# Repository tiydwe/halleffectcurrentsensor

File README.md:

# Handheld Hall Effect Current Sensor

This is a handheld hall effect current sensor, a device used to measure current without needing to directly touch the circuit being measured.

# Features
* Completely contained on one handheld case, including battery
* Self powered!
* OLED screen for easy measurement
* Two adjustable calibration resistors for easy calibration

# Assembly
The handheld hall effect current sensor is easily assembled with just 4 parts:
* The bottom part of case
* The battery, which sits in the bottom part of case
* The PCB, which goes between the top and bottom part of the case
* The top part of the case

It is held together with 4 M2 screws and 4 M2 nuts.

# Technical stuff

The hall effect voltage output is fed into an insturmentation amplifier to subtract it from the known zero current voltage and amplify the result. Both the gain and the reference voltage can be easily adjusted with two variable resistors on the PCB. The output of the insturmentation amplifier goes into a Seeed Studio nrf52840 microcontroller's ADC where it is processed. The current reading is then written onto the OLED.

The whole system is powered from a lipo battery, which is regulated to 3.3v by the Seeed Studio microcontroller. An additional [3.3v to 5v off-board converter](https://www.amazon.com/Comidox-Module-Voltage-Converter-0-9-5V/dp/B07L76KLRY/) is used to power the op amp and hall effect sensor.

# IMAGES
Full schematic:

PCB layout:

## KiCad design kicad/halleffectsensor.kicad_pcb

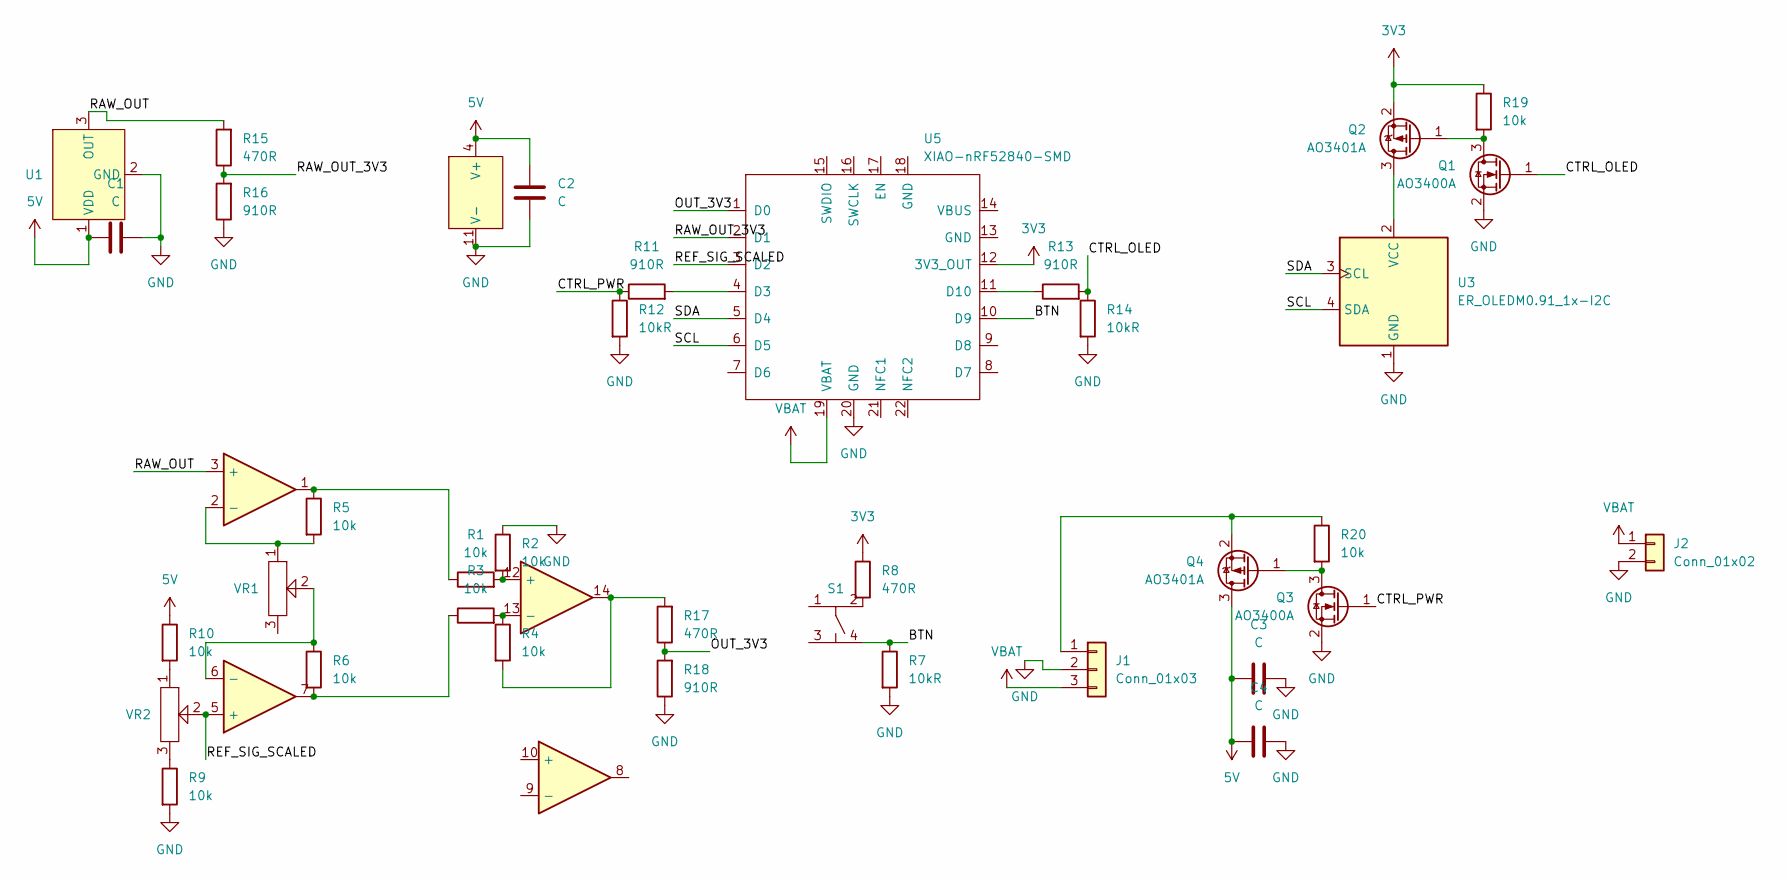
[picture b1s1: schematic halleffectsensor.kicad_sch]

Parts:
C1, C2, C3: C; C_1210_3225Metric_Pad1.33x2.70mm_HandSolder
C4: C; C_Radial_D4.0mm_H7.0mm_P1.50mm
J1: Conn_01x03; PinHeader_1x03_P1.27mm_Vertical
J2: Conn_01x02; PinHeader_1x02_P1.27mm_Vertical
Q1, Q3: AO3400A; SOT-23
Q2, Q4: AO3401A; SOT-23
R1, R2, R3, R4, R5, R6, R9, R10, R19, R20: 10k; R_1206_3216Metric_Pad1.30x1.75mm_HandSolder
R7, R12, R14: 10kR; R_1206_3216Metric_Pad1.30x1.75mm_HandSolder
R8, R15, R17: 470R; R_1206_3216Metric_Pad1.30x1.75mm_HandSolder
R11, R13, R16, R18: 910R; R_1206_3216Metric_Pad1.30x1.75mm_HandSolder
S1: SOIC-4
U1: TO-92S-3_L4.1-W1.7-P1.27-L
U3: ER_OLEDM0.91_1x-I2C; OLED-TH_L27.8-W27.2-P2.54_C9900033791
U4: SOP-14_L8.6-W3.9-P1.27-LS6.0-BL
U5: XIAO-nRF52840-SMD
VR1, VR2: Potentiometer_3_pi

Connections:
3V3: Q2.2 (S), R8.1, R19.1, U5.12 (3V3_OUT)
5V: C1.1, C2.2, C3.2, C4.2, Q4.3 (D), R10.1, U1.1 (VDD), U4.4 (V+)
/BTN: R7.1, S1.4, U5.10 (D9)
/CTRL_OLED: Q1.1 (G), R13.2, R14.1
/CTRL_PWR: Q3.1 (G), R11.1, R12.1
/OUT_3V3: R17.1, R18.2, U5.1 (D0)
/RAW_OUT: R15.2, U1.3 (OUT), U4.3 (+)
/RAW_OUT_3V3: R15.1, R16.2, U5.2 (D1)
/REF_SIG_SCALED: U4.5 (+), U5.3 (D2), VR2.2
/SCL: U3.4 (SDA), U5.6 (D5)
/SDA: U3.3 (SCL), U5.5 (D4)
GND: C1.2, C2.1, C3.1, C4.1, J1.2, J2.2, Q1.2 (S), Q3.2 (S), R2.1, R7.2, R9.2, R12.2, R14.2, R16.1, R18.1, U1.2 (GND), U3.1 (GND), U4.11 (V-), U5.20 (GND)
unnamed: J1.1, Q4.2 (S), R20.1
unnamed: Q1.3 (D), Q2.1 (G), R19.2
unnamed: Q2.3 (D), U3.2 (VCC)
unnamed: Q3.3 (D), Q4.1 (G), R20.2
unnamed: R1.1, R5.1, U4.1
unnamed: R3.1, R6.2, U4.7
unnamed: R8.2, S1.2
unnamed: R9.1, VR2.3
unnamed: R10.2, VR2.1
unnamed: R4.2, R17.2, U4.14
unnamed: R5.2, U4.2 (-), VR1.1
unnamed: R6.1, U4.6 (-), VR1.2
unnamed: R1.2, R2.2, U4.12 (+)
unnamed: R3.2, R4.1, U4.13 (-)
unnamed: R11.2, U5.4 (D3)
unnamed: R13.1, U5.11 (D10)
VBAT: J1.3, J2.1, U5.19 (VBAT)

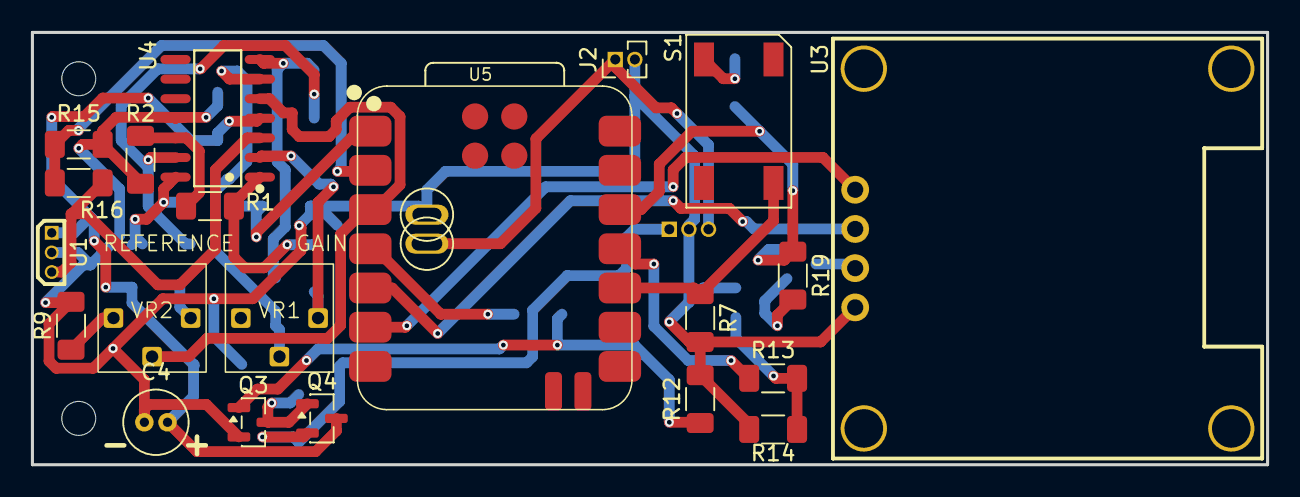
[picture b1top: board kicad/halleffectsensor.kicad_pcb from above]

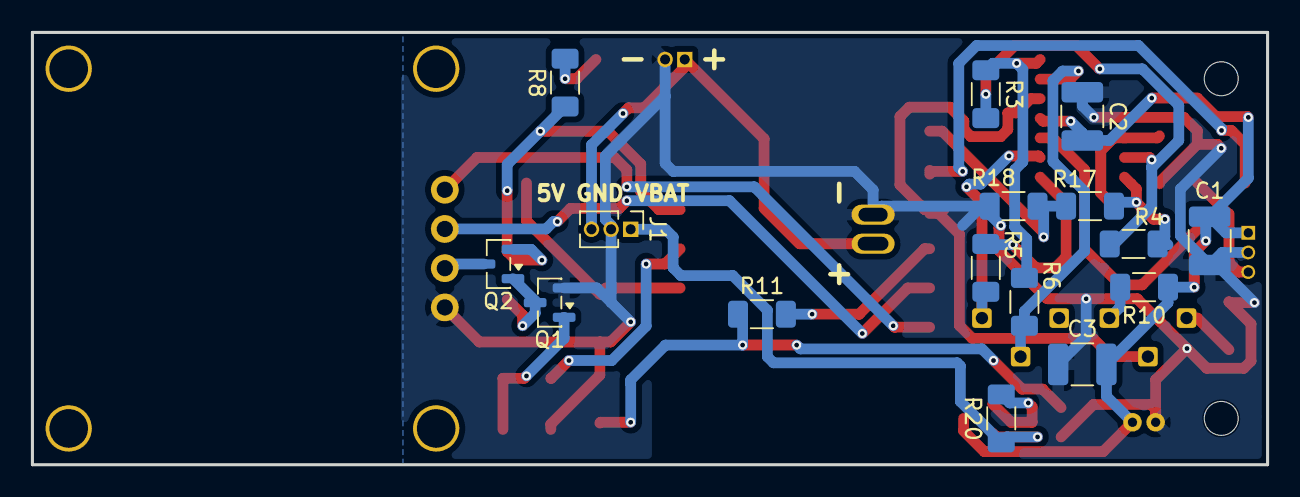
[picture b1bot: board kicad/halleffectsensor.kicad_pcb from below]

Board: 2 copper layers, 80.0 x 28.0 mm, 37 parts (16 on the bottom side), 29 nets.

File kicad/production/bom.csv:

Designator,Footprint,Quantity,Value,LCSC Part #
"C1, C2, C3",1210,3,C,
C4,C_Radial_D4.0mm_H7.0mm_P1.50mm,1,C,
J1,PinHeader_1x03_P1.27mm_Vertical,1,Conn_01x03,
J2,PinHeader_1x02_P1.27mm_Vertical,1,Conn_01x02,
"Q1, Q3",SOT-23,2,AO3400A,
"Q2, Q4",SOT-23,2,AO3401A,
"R1, R10, R19, R2, R20, R3, R4, R5, R6, R9",1206,10,10k,
"R11, R13, R16, R18",1206,4,910R,
"R12, R14, R7",1206,3,10kR,
"R15, R17, R8",1206,3,470R,
S1,SOIC-4,1,~,
U1,TO-92S-3_L4.1-W1.7-P1.27-L,1,~,
U3,OLED-TH_L27.8-W27.2-P2.54_C9900033791,1,ER_OLEDM0.91_1x-I2C,
U4,SOP-14_L8.6-W3.9-P1.27-LS6.0-BL,1,~,
U5,XIAO-nRF52840-SMD,1,XIAO-nRF52840-SMD,
"VR1, VR2",Potentiometer_3_pi,2,~,

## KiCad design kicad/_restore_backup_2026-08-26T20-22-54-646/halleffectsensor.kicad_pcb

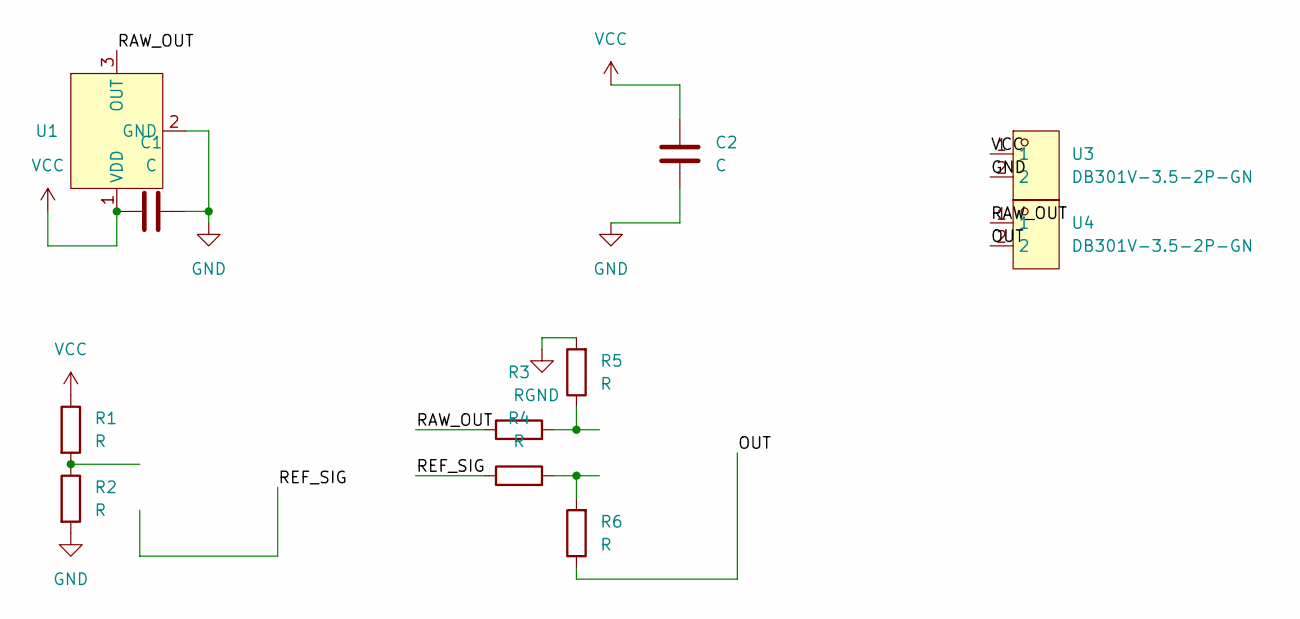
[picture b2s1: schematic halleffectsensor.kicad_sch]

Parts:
C1, C2: C; C_1210_3225Metric_Pad1.33x2.70mm_HandSolder
R1, R2, R3, R4, R5, R6: R; R_Axial_DIN0204_L3.6mm_D1.6mm_P7.62mm_Horizontal
U1: TO-92S-3_L4.1-W1.7-P1.27-L
U3, U4: DB301V-3.5-2P-GN; CONN-TH_DB301V-3.5-2P-GN; LCSC Part C695629

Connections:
/OUT: R6.1, U4.2; also elsewhere on the board
/RAW_OUT: R3.1, U1.3 (OUT), U4.1
/REF_SIG: R4.1; also elsewhere on the board
GND: C1.2, C2.1, R2.2, R5.2, U1.2 (GND), U3.2; also elsewhere on the board
unnamed 4: R1.2, R2.1; also elsewhere on the board
unnamed 5: R3.2, R5.1; also elsewhere on the board
unnamed 6: R4.2, R6.2; also elsewhere on the board
VCC: C1.1, C2.2, R1.1, U1.1 (VDD), U3.1; also elsewhere on the board

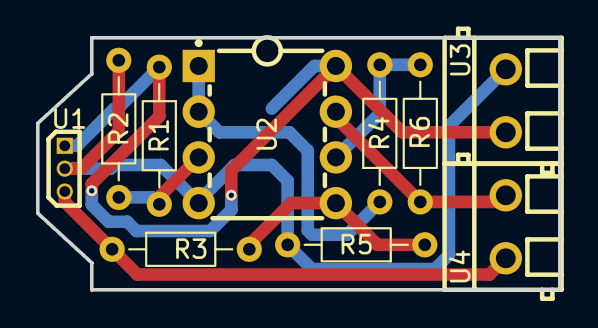
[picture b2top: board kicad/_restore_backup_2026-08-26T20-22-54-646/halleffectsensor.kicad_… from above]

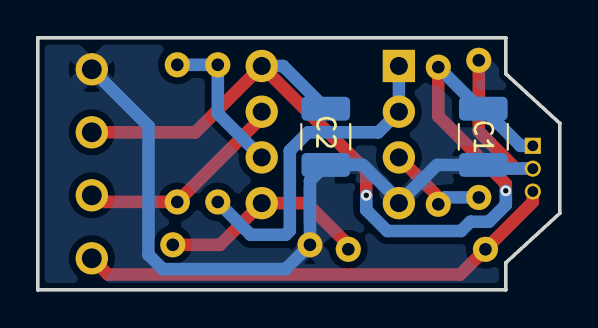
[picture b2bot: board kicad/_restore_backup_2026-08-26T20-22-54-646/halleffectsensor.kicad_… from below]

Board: 2 copper layers, 29.0 x 14.0 mm, 12 parts (2 on the bottom side), 8 nets.

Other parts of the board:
U2: COS5532DT; DIP-8_L9.3-W6.4-P2.54-LS7.6-BL

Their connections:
/OUT: U2.7; also elsewhere on the board
/REF_SIG: U2.1, U2.2 (-); also elsewhere on the board
GND: U2.4 (V-); also elsewhere on the board
unnamed 4: U2.3 (+); also elsewhere on the board
unnamed 5: U2.5 (+); also elsewhere on the board
unnamed 6: U2.6 (-); also elsewhere on the board
VCC: U2.8 (V+); also elsewhere on the board

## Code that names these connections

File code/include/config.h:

#ifndef CONFIG_H
#define CONFIG_H

#include <Arduino.h>

// PINS
#define OUT_3V3 A0
#define RAW_OUT_3V3 A1
#define REF_SIG_SCALED A2
#define CTRL_PWR D3
#define CTRL_OLED D10
//#define SDA 5
//#define SCL 6
#define BTN D9

// OLED
#define OLED_SCREEN_WIDTH 128
#define OLED_SCREEN_HEIGHT 64
#define OLED_ADDRESS 0x3C
#define OLED_RESET_PIN -1

// SENSOR
#define CONVERT_3V3_5V (((long double)5.0) / 3.3)
#define READ_CNT 10

#endif
